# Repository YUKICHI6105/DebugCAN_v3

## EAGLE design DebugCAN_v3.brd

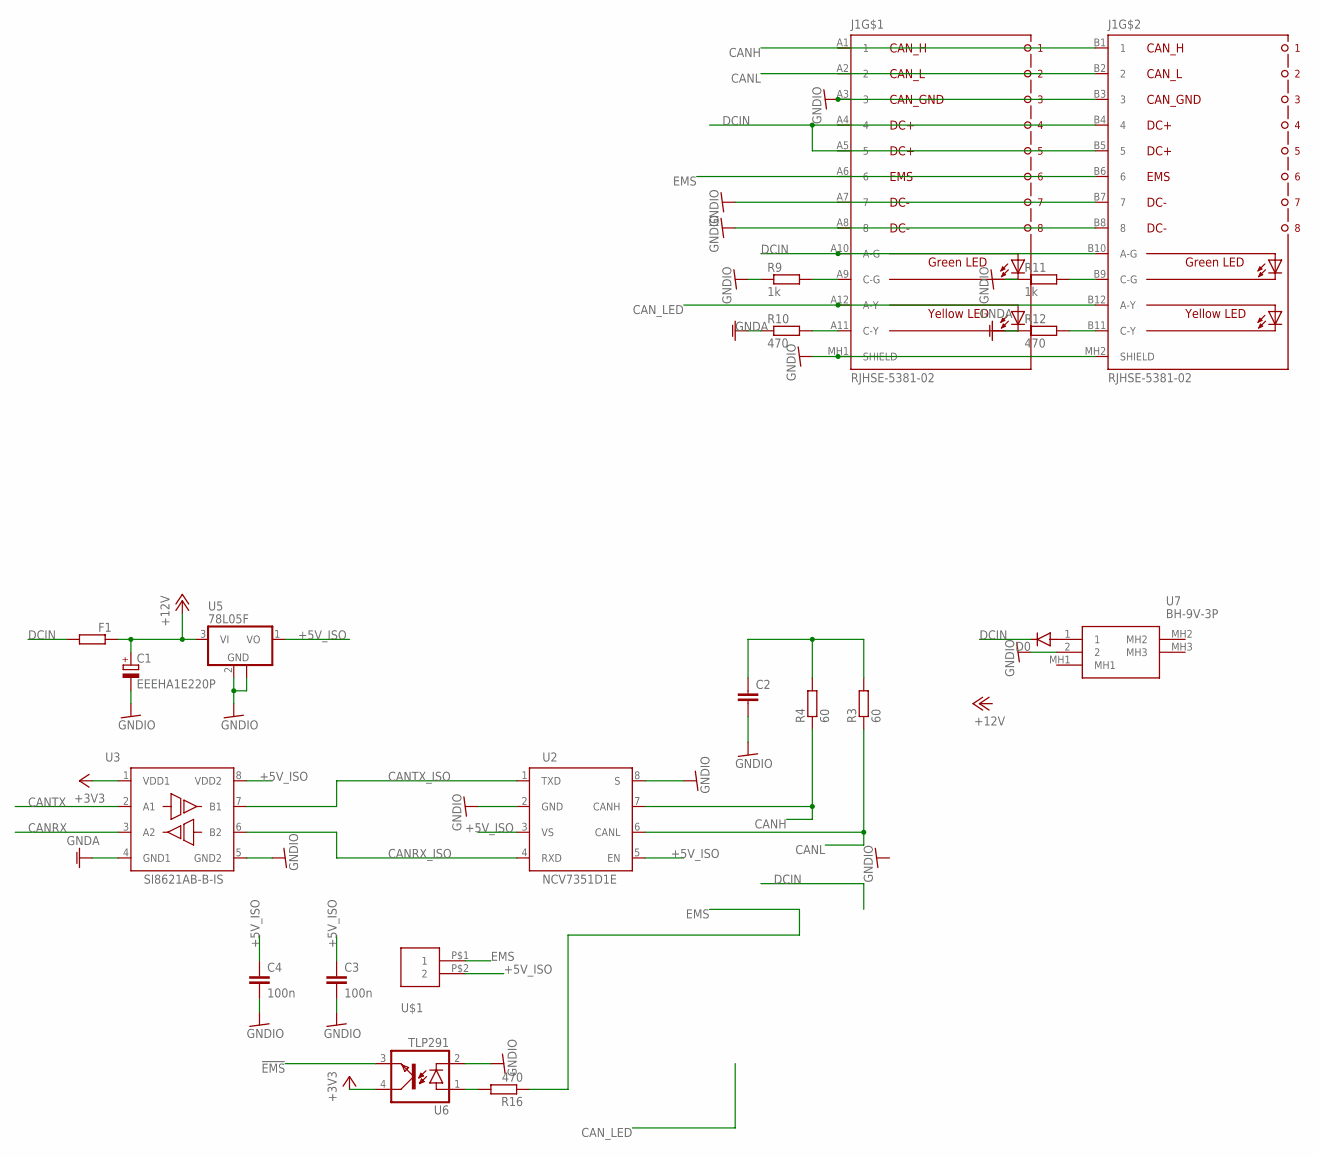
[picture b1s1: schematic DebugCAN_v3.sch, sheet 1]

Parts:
C1: EEEHA1E220P; 153CLV-0605
C2: C-EUC0603; C0603
C3, C4: 100n; C0603
D0: DIODE-SOD123; SOD123
F1: R-EU_R1206; R1206
J1: RJHSE-5381-02; RJHSE538102
R3, R4: 60; R0603
R9, R11: 1k; R0603
R10, R12, R16: 470; R0603
U2: NCV7351D1E; SO08
U3: SI8621AB-B-IS; SO08
U5: 78L05F; SOT89
U6: TLP291; MINI-FLAT-4
U7: BH-9V-3P; BH9V3P
U$1: XH-2-STRAIGHT; CON-XH-2-STRAIGHT

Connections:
!EMS: U6.3 (EMIT); also elsewhere on the board
+3V3: U3.1 (VDD1), U6.4 (COL); also elsewhere on the board
+5V_ISO: C3.1, C4.1, U2.3 (VS), U2.5 (EN), U3.8 (VDD2), U5.1 (VO), U$1.P$2 (2)
+12V: C1.+, F1.1, U5.3 (VI)
CANH: J1.A1 (1), J1.B1 (1), R4.1, U2.7 (CANH)
CANL: J1.A2 (2), J1.B2 (2), R3.1, U2.6 (CANL)
CANRX: U3.3 (A2); also elsewhere on the board
CANRX_ISO: U2.4 (RXD), U3.6 (B2)
CANTX: U3.2 (A1); also elsewhere on the board
CANTX_ISO: U2.1 (TXD), U3.7 (B1)
CAN_LED: J1.A12 (A-Y), J1.B12 (A-Y); also elsewhere on the board
DCIN: D0.C, F1.2, J1.A4 (4), J1.A5 (5), J1.A10 (A-G), J1.B4 (4), J1.B5 (5), J1.B10 (A-G)
EMS: J1.A6 (6), J1.B6 (6), R16.1, U$1.P$1 (1)
GNDA: R10.1, R12.1, U3.4 (GND1); also elsewhere on the board
GNDIO: C1.-, C2.2, C3.2, C4.2, J1.A3 (3), J1.A7 (7), J1.A8 (8), J1.B3 (3), J1.B7 (7), J1.B8 (8), J1.MH1 (SHIELD), J1.MH2 (SHIELD), R9.1, R11.1, U2.2 (GND), U2.8 (S), U3.5 (GND2), U5.2 (GND), U5.2@1 (GND), U6.2 (C), U7.2
unnamed: J1.A9 (C-G), R9.2
unnamed: D0.A, U7.1
unnamed: C2.1, R3.2, R4.2
unnamed: J1.A11 (C-Y), R10.2
unnamed: J1.B11 (C-Y), R12.2
unnamed: J1.B9 (C-G), R11.2
unnamed: R16.2, U6.1 (A)

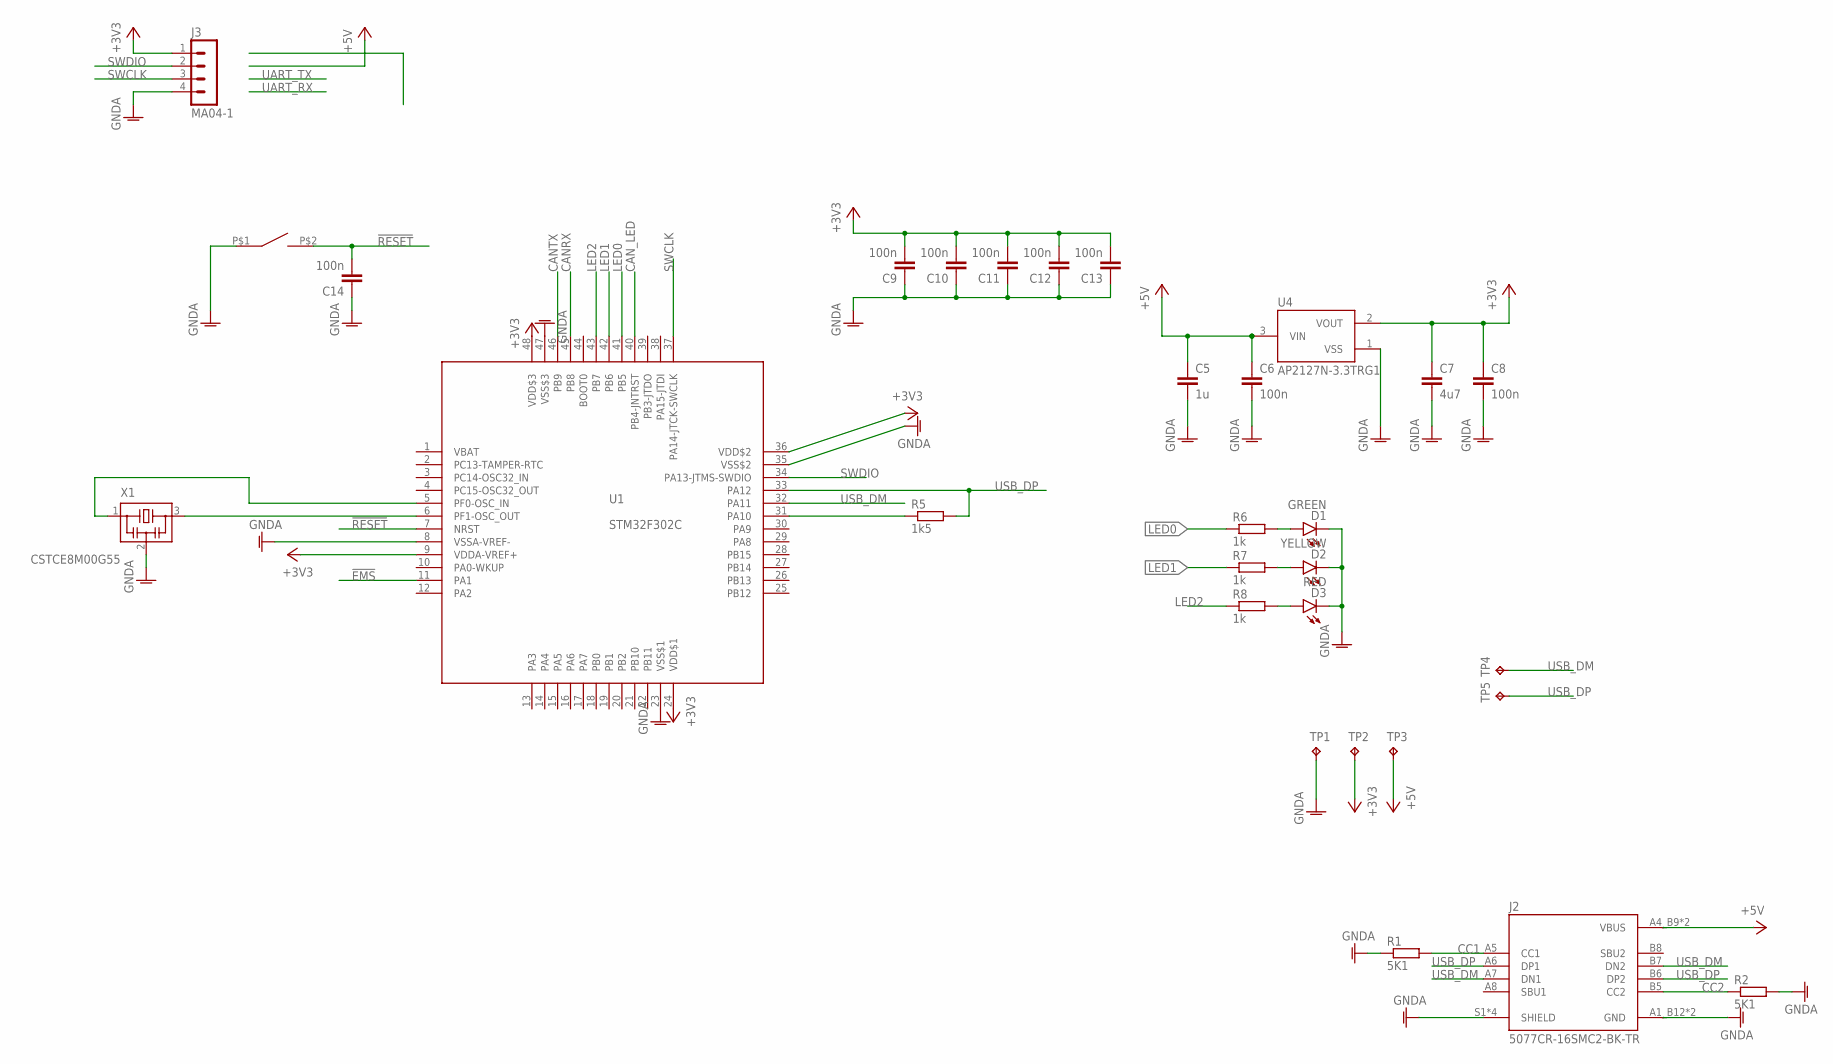
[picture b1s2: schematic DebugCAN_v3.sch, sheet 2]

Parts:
C5: 1u; C0603
C6, C8, C9, C10, C11, C12, C13, C14: 100n; C0603
C7: 4u7; C0805
D1: GREEN; CHIPLED_0805
D2: YELLOW; CHIPLED_0805
D3: RED; CHIPLED_0805
J2: 5077CR-16SMC2-BK-TR; NELTRON_5077CR-16SMC2-BK-TR
J3: MA04-1
R1, R2: 5K1; R0603
R5: 1k5; R0603
R6, R7, R8: 1k; R0603
S1: SWITCH_TACTILETOP; SWITCH_TACTILE_3X6
TP1, TP2, TP3, TP4, TP5: TPB1,27; B1,27
U1: STM32F302C; LQFP48
U4: AP2127N-3.3TRG1; SOT95P240X110-3
X1: CSTCE8M00G55

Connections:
!EMS: U1.11 (PA1); also elsewhere on the board
!RESET: C14.2, S1.P$2 (2), U1.7 (NRST)
+3V3: C7.1, C8.1, C9.2, C10.2, C11.2, C12.2, C13.2, J3.1, TP2.TP, U1.9 (VDDA-VREF+), U1.24 (VDD$1), U1.36 (VDD$2), U1.48 (VDD$3), U4.2 (VOUT); also elsewhere on the board
+5V: C5.1, C6.1, J2.A4_B9 (VBUS), J2.B4_A9 (VBUS), TP3.TP, U4.3 (VIN)
CANRX: U1.45 (PB8); also elsewhere on the board
CANTX: U1.46 (PB9); also elsewhere on the board
CAN_LED: U1.40 (PB4-JNTRST); also elsewhere on the board
CC1: J2.A5 (CC1), R1.2
CC2: J2.B5 (CC2), R2.1
GNDA: C5.2, C6.2, C7.2, C8.2, C9.1, C10.1, C11.1, C12.1, C13.1, C14.1, D1.C, D2.C, D3.C, J2.A1_B12 (GND), J2.B1_A12 (GND), J2.S1 (SHIELD), J2.S2 (SHIELD), J2.S3 (SHIELD), J2.S4 (SHIELD), J3.4, R1.1, R2.2, S1.P$1 (1), TP1.TP, U1.8 (VSSA-VREF-), U1.23 (VSS$1), U1.35 (VSS$2), U1.47 (VSS$3), U4.1 (VSS), X1.2; also elsewhere on the board
LED0: R6.1, U1.41 (PB5)
LED1: R7.1, U1.42 (PB6)
LED2: R8.1, U1.43 (PB7)
unnamed: D2.A, R7.2
unnamed: D1.A, R6.2
unnamed: U1.6 (PF1-OSC_OUT), X1.3
unnamed: U1.5 (PF0-OSC_IN), X1.1
unnamed: R5.1, U1.31 (PA10)
unnamed: D3.A, R8.2
SWCLK: J3.3, U1.37 (PA14-JTCK-SWCLK)
SWDIO: J3.2, U1.34 (PA13-JTMS-SWDIO)
USB_DM: J2.A7 (DN1), J2.B7 (DN2), TP4.TP, U1.32 (PA11)
USB_DP: J2.A6 (DP1), J2.B6 (DP2), R5.2, TP5.TP, U1.33 (PA12)

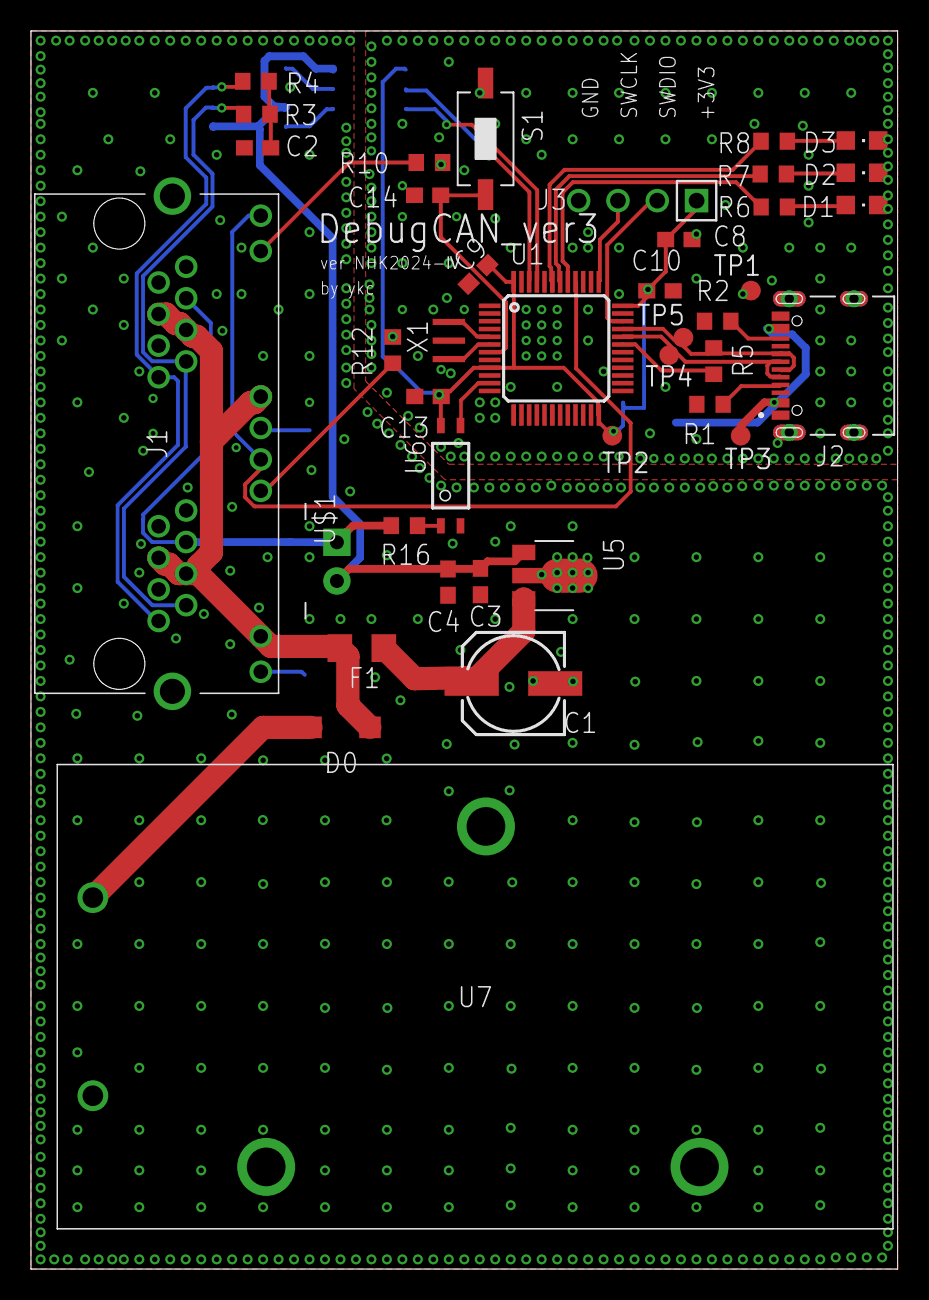
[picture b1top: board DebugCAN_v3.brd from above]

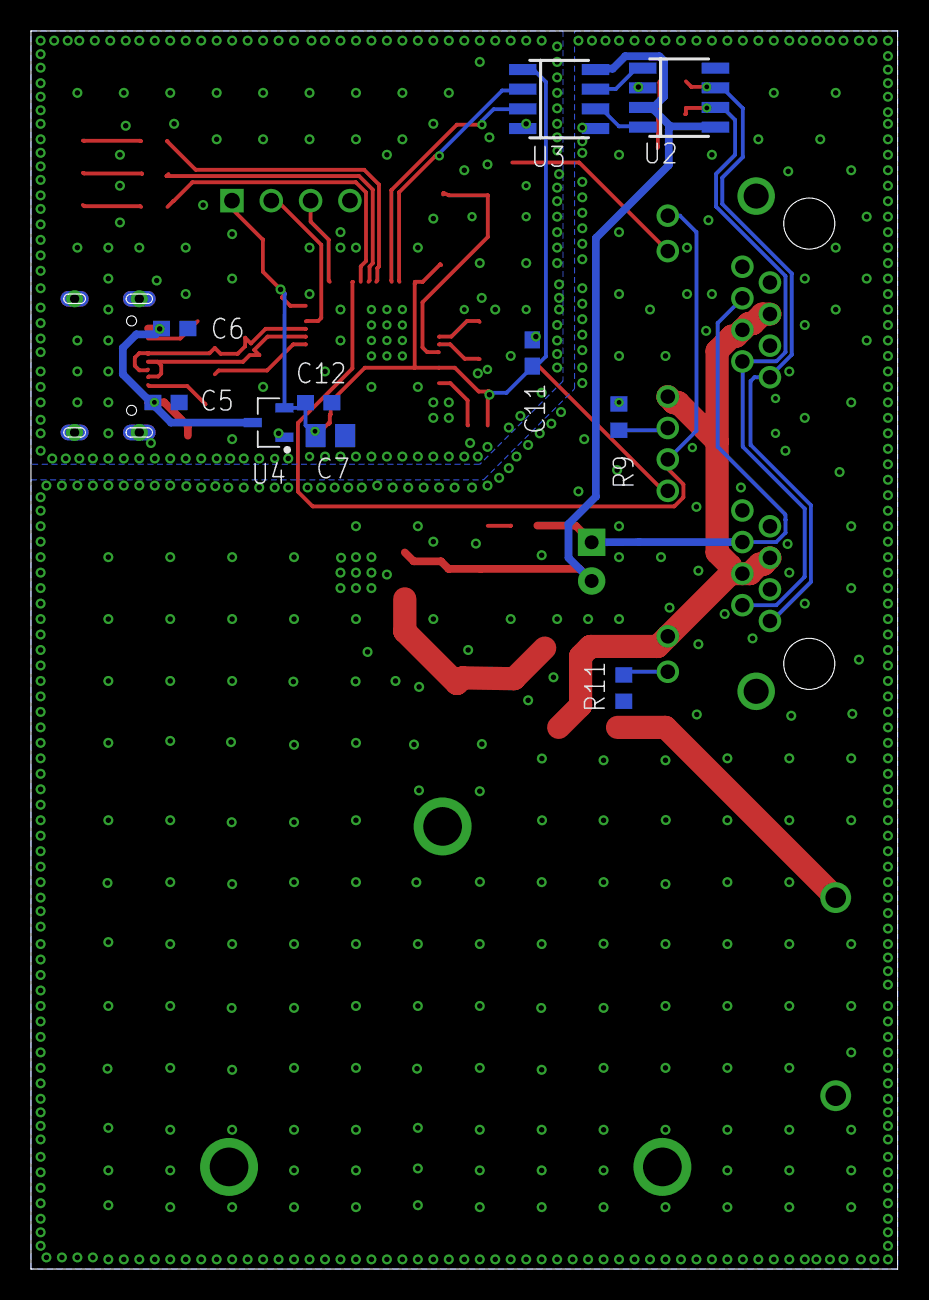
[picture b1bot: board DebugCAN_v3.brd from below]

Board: 2 copper layers, 56.0 x 80.0 mm, 50 parts (10 on the bottom side), 39 nets.

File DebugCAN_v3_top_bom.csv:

Comment,Designator,Footprint,LCSC Part #
1k,R6 R7 R8,R0603,
1k5,R5,R0603,
5K1,R1 R2,R0603,
60,R3 R4,R0603,
78L05F,U5,SOT89,
100n,C3 C4 C8 C9 C10 C13 C14,C0603,
470,R10 R12 R16,R0603,
5077CR-16SMC2-BK-TR,J2,NELTRON_5077CR-16SMC2-BK-TR,
CSTCE8M00G55,X1,CSTCE8M00G55,
EEEHA1E220P,C1,153CLV-0605,
GREEN,D1,CHIPLED_0805,
RED,D3,CHIPLED_0805,
STM32F302C,U1,LQFP48,
SWITCH_TACTILETOP,S1,SWITCH_TACTILE_3X6,
TLP291,U6,MINI-FLAT-4,
TPB1 27,TP1,B1 27,
TPB1 27,TP2,B1 27,
TPB1 27,TP3,B1 27,
TPB1 27,TP4,B1 27,
TPB1 27,TP5,B1 27,
YELLOW,D2,CHIPLED_0805,

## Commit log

2023-12-18 final update
